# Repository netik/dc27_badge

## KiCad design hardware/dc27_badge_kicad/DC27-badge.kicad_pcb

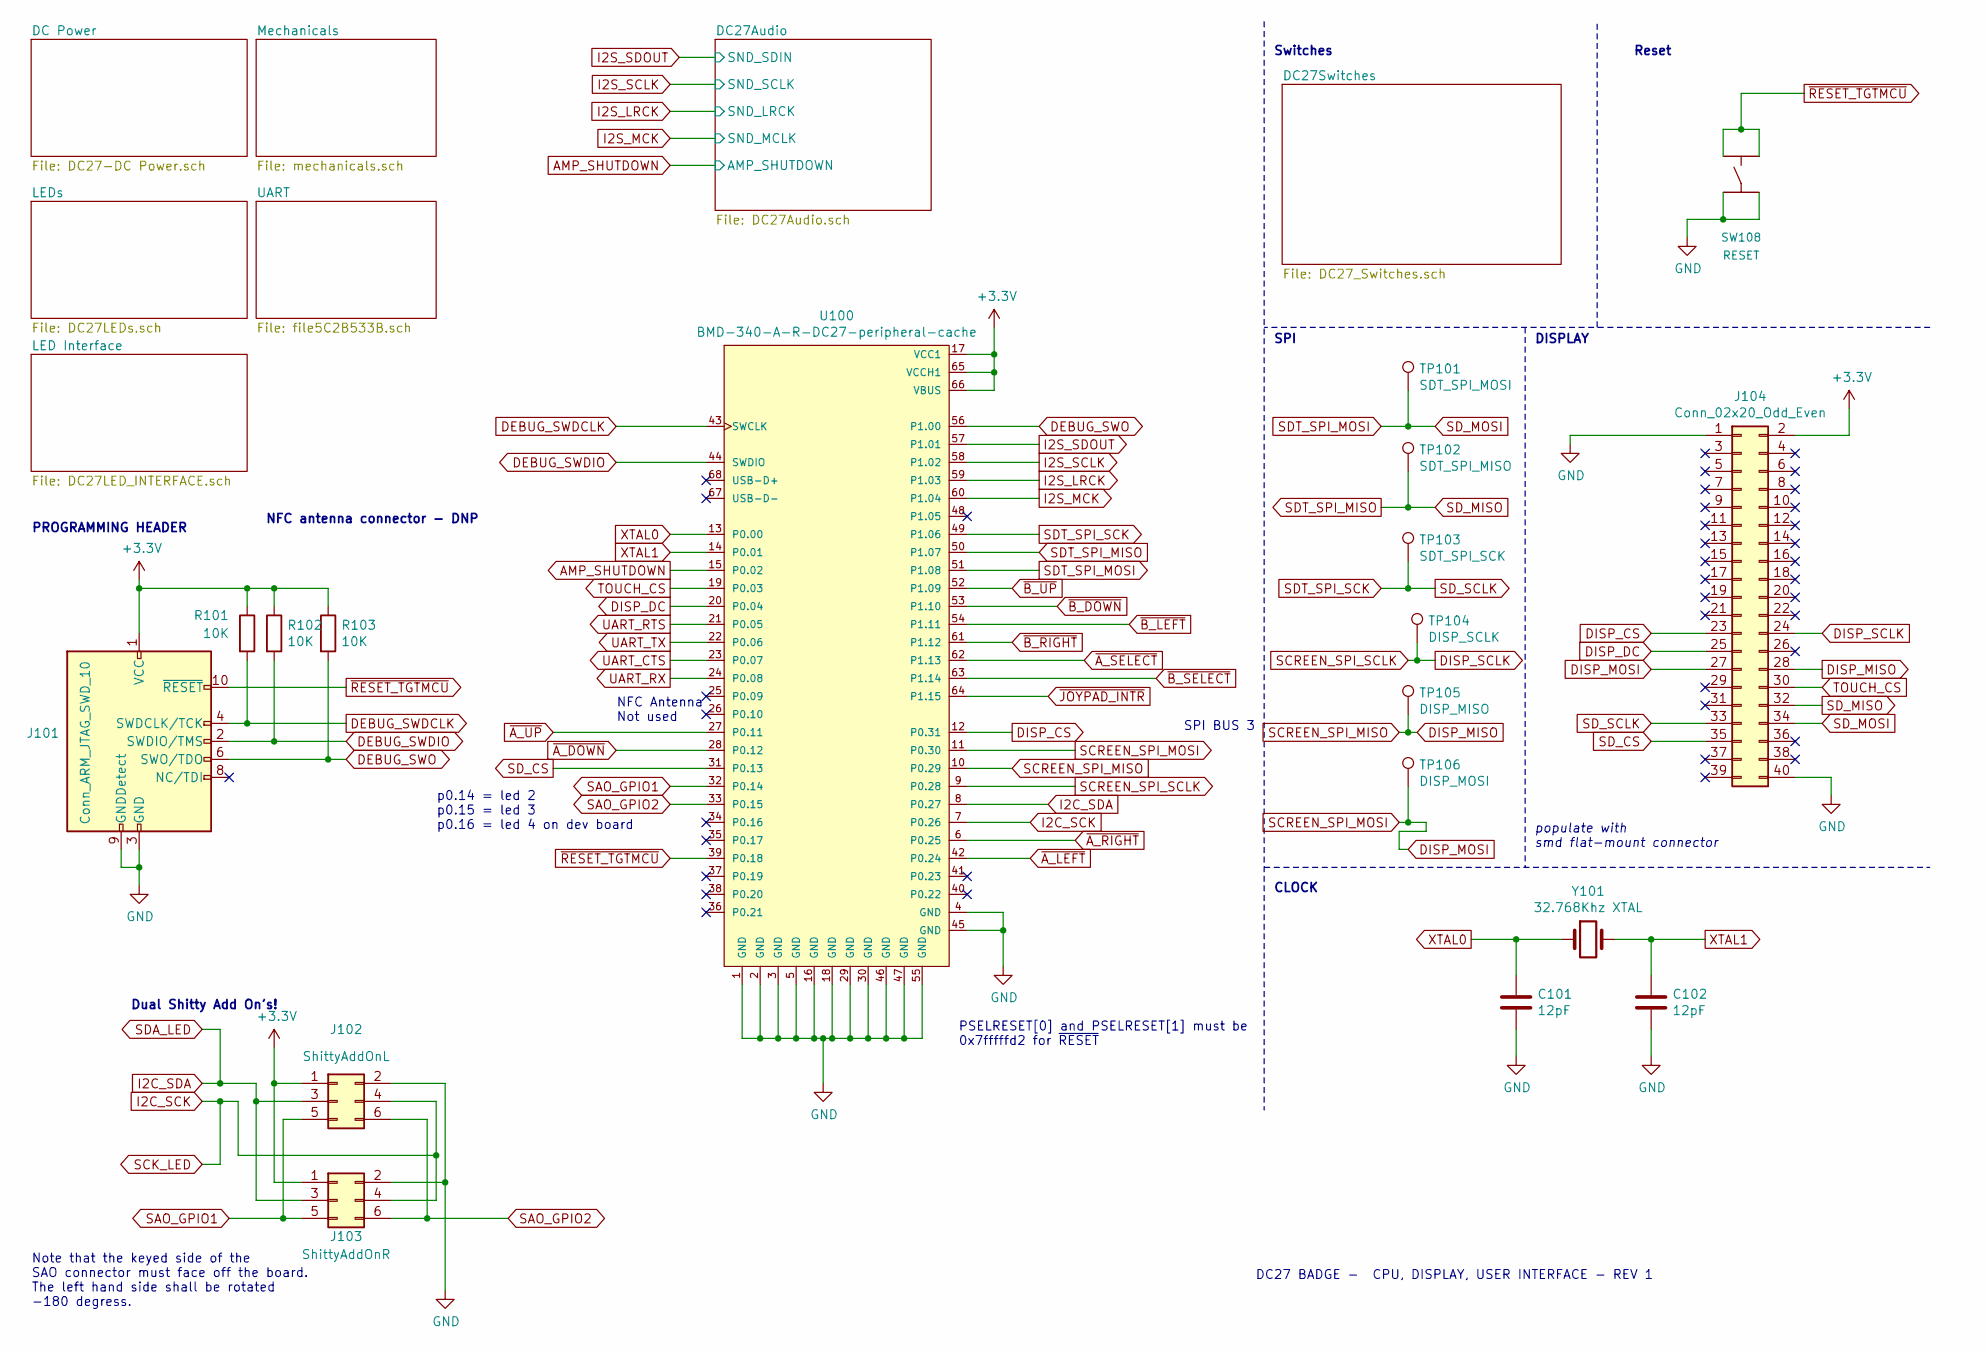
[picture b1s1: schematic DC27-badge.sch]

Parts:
C101, C102: 12pF; C_0805_2012Metric
J101: Conn_ARM_JTAG_SWD_10; PinHeader_2x05_P1.27mm_Vertical_SMD
J102: ShittyAddOnL; PinSocket_2x03_P2.54mm_Vertical
J103: ShittyAddOnR; PinSocket_2x03_P2.54mm_Vertical
J104: Conn_02x20_Odd_Even; SAMTEC-SSM-120-X-DV
R101, R102, R103: 10K; R_0603_1608Metric
SW108: RESET; MF_Switches-TACT4.2MM
TP101: SDT_SPI_MOSI; PinHeader_1x01_P2.54mm_Vertical
TP102: SDT_SPI_MISO; PinHeader_1x01_P2.54mm_Vertical
TP103: SDT_SPI_SCK; PinHeader_1x01_P2.54mm_Vertical
TP104: DISP_SCLK; PinHeader_1x01_P2.54mm_Vertical
TP105: DISP_MISO; PinHeader_1x01_P2.54mm_Vertical
TP106: DISP_MOSI; PinHeader_1x01_P2.54mm_Vertical
U100: BMD-340-A-R-DC27-peripheral-cache; RIGADO_BMD-340-A-R
Y101: 32.768Khz XTAL; Crystal_SMD_MicroCrystal_CC7V-T1A-2Pin_3.2x1.5mm

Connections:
AMP_SHUTDOWN: U100.15 (P0.02); also elsewhere on the board
AVCC: J101.1 (VCC), J102.1, J103.1, J104.2, R101.1, R102.1, R103.1, U100.17 (VCC1), U100.65 (VCCH1), U100.66 (VBUS); also elsewhere on the board
DEBUG_SWDCLK: J101.4 (SWDCLK/TCK), R101.2, U100.43 (SWCLK)
DEBUG_SWDIO: J101.2 (SWDIO/TMS), R102.2, U100.44 (SWDIO)
DEBUG_SWO: J101.6 (SWO/TDO), R103.2, U100.56 (P1.00)
DISP_CS: J104.23, U100.12 (P0.31)
DISP_DC: J104.25, U100.20 (P0.04)
DISP_MISO: J104.28, TP105.1, U100.10 (P0.29)
DISP_MOSI: J104.27, TP106.1, U100.11 (P0.30)
DISP_SCLK: J104.24, TP104.1, U100.9 (P0.28)
GND: C101.2, C102.2, J101.3 (GND), J101.5 (GND), J101.9 (GNDDetect), J102.2, J103.2, J104.1, J104.40, SW108.P$3, SW108.P$4, U100.1 (GND), U100.2 (GND), U100.3 (GND), U100.4 (GND), U100.5 (GND), U100.16 (GND), U100.18 (GND), U100.29 (GND), U100.30 (GND), U100.45 (GND), U100.46 (GND), U100.47 (GND), U100.55 (GND); also elsewhere on the board
I2C_SCK: J102.4, J103.4, U100.7 (P0.26); also elsewhere on the board
I2C_SDA: J102.3, J103.3, U100.8 (P0.27); also elsewhere on the board
I2S_LRCK: U100.59 (P1.03); also elsewhere on the board
I2S_MCK: U100.60 (P1.04); also elsewhere on the board
I2S_SCLK: U100.58 (P1.02); also elsewhere on the board
I2S_SDOUT: U100.57 (P1.01); also elsewhere on the board
SAO_GPIO1: J102.5, J103.5, U100.32 (P0.14)
SAO_GPIO2: J102.6, J103.6, U100.33 (P0.15)
SDT_SPI_MISO: J104.32, TP102.1, U100.50 (P1.07)
SDT_SPI_MOSI: J104.34, TP101.1, U100.51 (P1.08)
SDT_SPI_SCK: J104.33, TP103.1, U100.49 (P1.06)
SD_CS: J104.35, U100.31 (P0.13)
TOUCH_CS: J104.30, U100.19 (P0.03)
UART_CTS: U100.23 (P0.07); also elsewhere on the board
UART_RTS: U100.21 (P0.05); also elsewhere on the board
UART_RX: U100.24 (P0.08); also elsewhere on the board
UART_TX: U100.22 (P0.06); also elsewhere on the board
XTAL0: C101.1, U100.13 (P0.00), Y101.1
XTAL1: C102.1, U100.14 (P0.01), Y101.2
~A_DOWN: U100.28 (P0.12); also elsewhere on the board
~A_LEFT: U100.42 (P0.24); also elsewhere on the board
~A_RIGHT: U100.6 (P0.25); also elsewhere on the board
~A_SELECT: U100.62 (P1.13); also elsewhere on the board
~A_UP: U100.27 (P0.11); also elsewhere on the board
~B_DOWN: U100.53 (P1.10); also elsewhere on the board
~B_LEFT: U100.54 (P1.11); also elsewhere on the board
~B_RIGHT: U100.61 (P1.12); also elsewhere on the board
~B_SELECT: U100.63 (P1.14); also elsewhere on the board
~B_UP: U100.52 (P1.09); also elsewhere on the board
~JOYPAD_INTR: U100.64 (P1.15); also elsewhere on the board
~RESET_TGTMCU: J101.10 (~RESET~), SW108.P$1, SW108.P$2, U100.39 (P0.18)

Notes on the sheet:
DISPLAY
PROGRAMMING HEADER
populate with smd flat-mount connector
PSELRESET[0] and PSELRESET[1] must be 0x7fffffd2 for ~RESET
CLOCK
SPI
SPI BUS 3
NFC antenna connector - DNP
p0.14 = led 2 p0.15 = led 3 p0.16 = led 4 on dev board
DC27 BADGE - CPU, DISPLAY, USER INTERFACE - REV 1
NFC Antenna Not used
Dual Shitty Add On’s!
Switches
Reset
Note that the keyed side of the SAO connector must face off the board. The left hand side shall be rotated -180 degress.

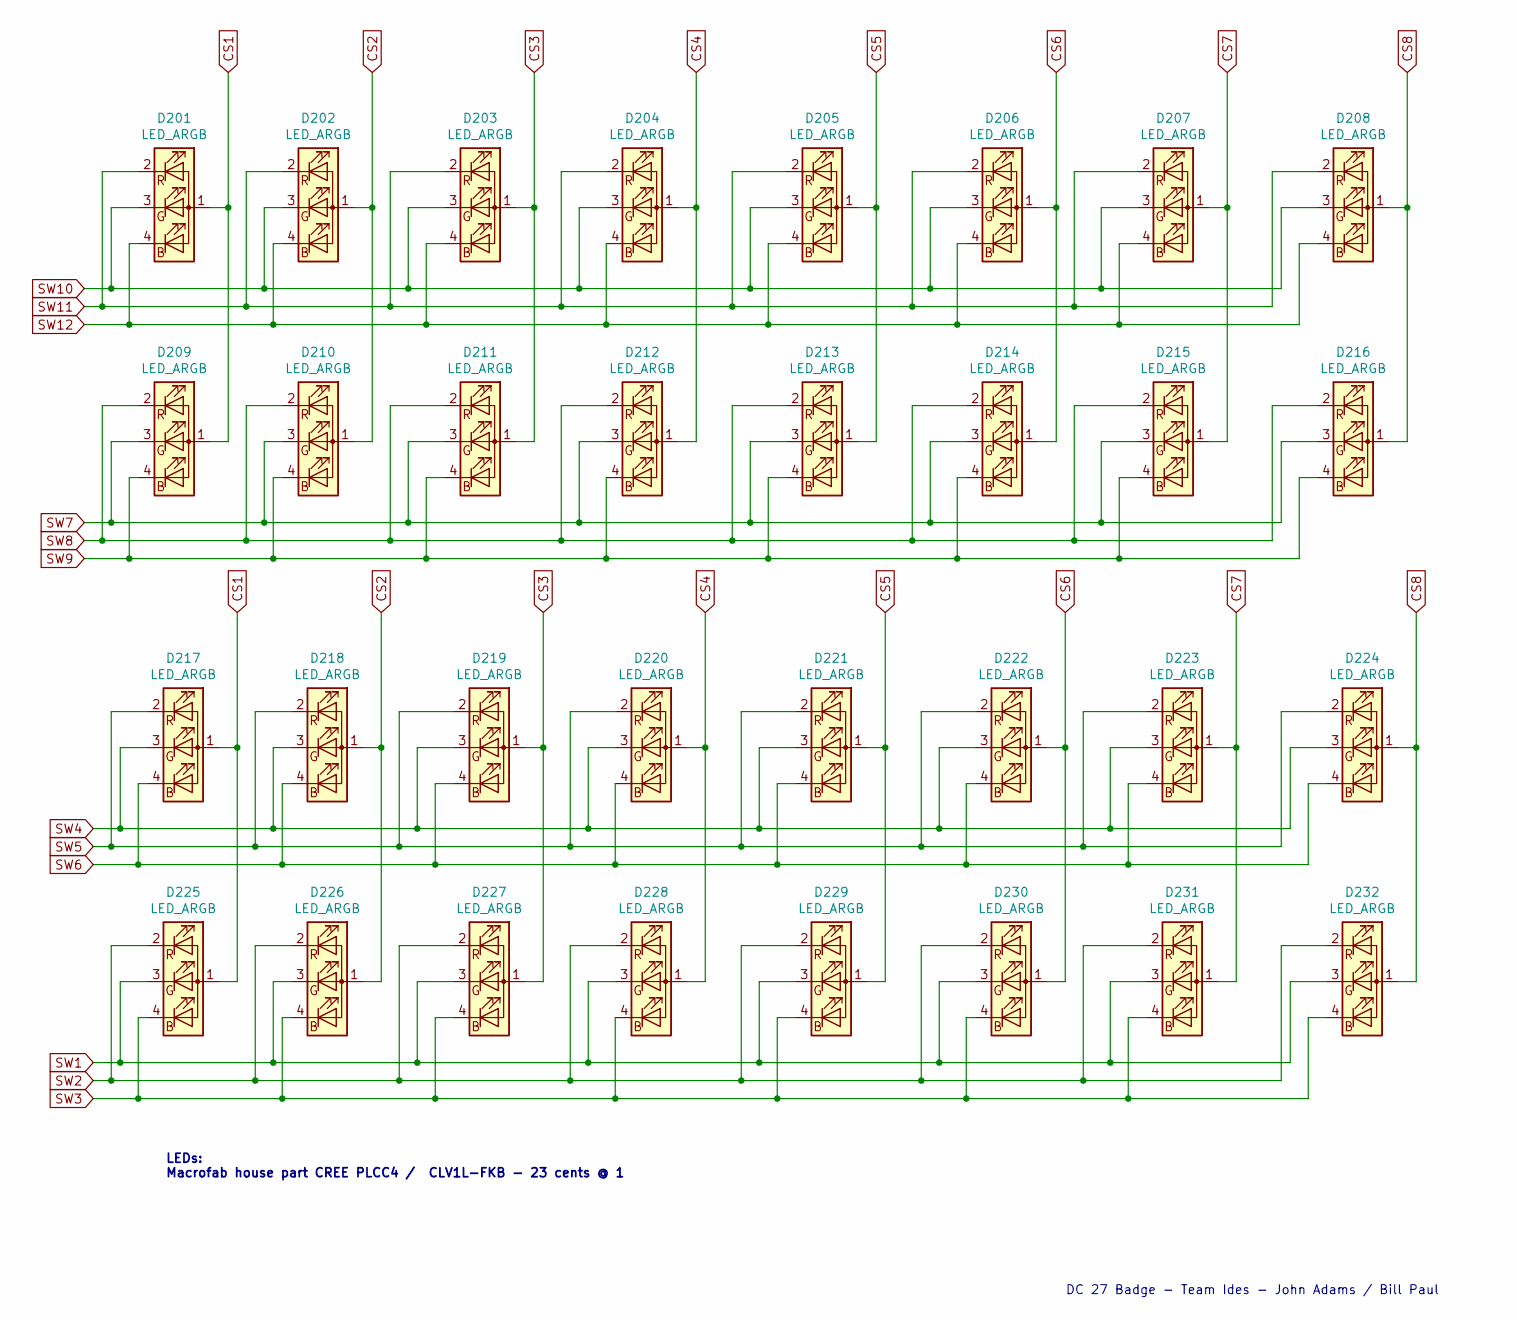
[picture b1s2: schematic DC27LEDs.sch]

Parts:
D201, D202, D203, D204, D205, D206, D207, D208, D209, D210, D211, D212, D213, D214, D215, D216, D217, D218, D219, D220, D221, D222, D223, D224, D225, D226, D227, D228, D229, D230, D231, D232: LED_ARGB; LED_Cree-PLCC4_3.2x2.8mm_CCW

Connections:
CS1: D201.1 (A), D209.1 (A), D217.1 (A), D225.1 (A); also elsewhere on the board
CS2: D202.1 (A), D210.1 (A), D218.1 (A), D226.1 (A); also elsewhere on the board
CS3: D203.1 (A), D211.1 (A), D219.1 (A), D227.1 (A); also elsewhere on the board
CS4: D204.1 (A), D212.1 (A), D220.1 (A), D228.1 (A); also elsewhere on the board
CS5: D205.1 (A), D213.1 (A), D221.1 (A), D229.1 (A); also elsewhere on the board
CS6: D206.1 (A), D214.1 (A), D222.1 (A), D230.1 (A); also elsewhere on the board
CS7: D207.1 (A), D215.1 (A), D223.1 (A), D231.1 (A); also elsewhere on the board
CS8: D208.1 (A), D216.1 (A), D224.1 (A), D232.1 (A); also elsewhere on the board
SW1: D225.3 (GK), D226.3 (GK), D227.3 (GK), D228.3 (GK), D229.3 (GK), D230.3 (GK), D231.3 (GK), D232.3 (GK); also elsewhere on the board
SW2: D225.2 (RK), D226.2 (RK), D227.2 (RK), D228.2 (RK), D229.2 (RK), D230.2 (RK), D231.2 (RK), D232.2 (RK); also elsewhere on the board
SW3: D225.4 (BK), D226.4 (BK), D227.4 (BK), D228.4 (BK), D229.4 (BK), D230.4 (BK), D231.4 (BK), D232.4 (BK); also elsewhere on the board
SW4: D217.3 (GK), D218.3 (GK), D219.3 (GK), D220.3 (GK), D221.3 (GK), D222.3 (GK), D223.3 (GK), D224.3 (GK); also elsewhere on the board
SW5: D217.2 (RK), D218.2 (RK), D219.2 (RK), D220.2 (RK), D221.2 (RK), D222.2 (RK), D223.2 (RK), D224.2 (RK); also elsewhere on the board
SW6: D217.4 (BK), D218.4 (BK), D219.4 (BK), D220.4 (BK), D221.4 (BK), D222.4 (BK), D223.4 (BK), D224.4 (BK); also elsewhere on the board
SW7: D209.3 (GK), D210.3 (GK), D211.3 (GK), D212.3 (GK), D213.3 (GK), D214.3 (GK), D215.3 (GK), D216.3 (GK); also elsewhere on the board
SW8: D209.2 (RK), D210.2 (RK), D211.2 (RK), D212.2 (RK), D213.2 (RK), D214.2 (RK), D215.2 (RK), D216.2 (RK); also elsewhere on the board
SW9: D209.4 (BK), D210.4 (BK), D211.4 (BK), D212.4 (BK), D213.4 (BK), D214.4 (BK), D215.4 (BK), D216.4 (BK); also elsewhere on the board
SW10: D201.3 (GK), D202.3 (GK), D203.3 (GK), D204.3 (GK), D205.3 (GK), D206.3 (GK), D207.3 (GK), D208.3 (GK); also elsewhere on the board
SW11: D201.2 (RK), D202.2 (RK), D203.2 (RK), D204.2 (RK), D205.2 (RK), D206.2 (RK), D207.2 (RK), D208.2 (RK); also elsewhere on the board
SW12: D201.4 (BK), D202.4 (BK), D203.4 (BK), D204.4 (BK), D205.4 (BK), D206.4 (BK), D207.4 (BK), D208.4 (BK); also elsewhere on the board

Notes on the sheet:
LEDs: Macrofab house part CREE PLCC4 / CLV1L-FKB - 23 cents @ 1
DC 27 Badge - Team Ides - John Adams / Bill Paul

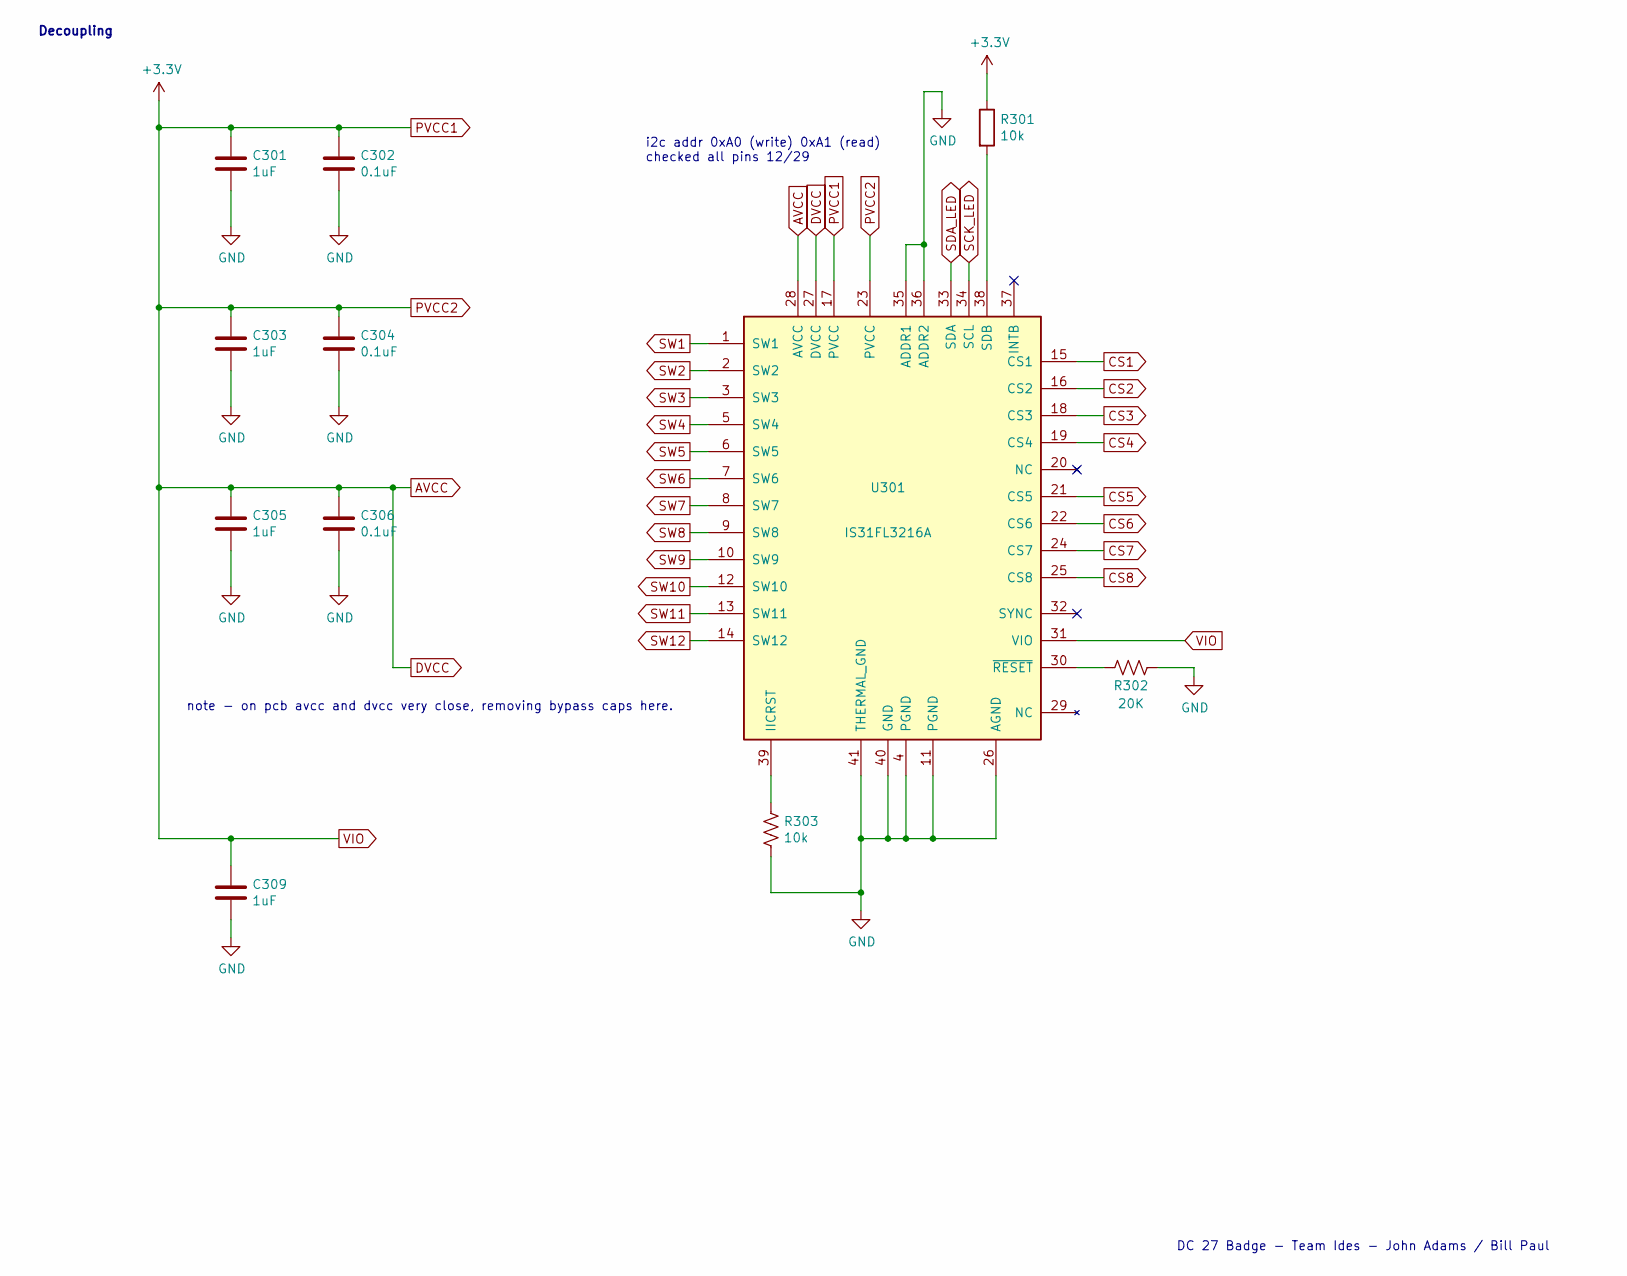
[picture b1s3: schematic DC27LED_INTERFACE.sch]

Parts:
C301, C303, C305, C309: 1uF; C_0603_1608Metric
C302, C304, C306: 0.1uF; C_0603_1608Metric
R301, R303: 10k; R_0603_1608Metric
R302: 20K; R_0603_1608Metric
U301: IS31FL3216A; QFN-40-1EP_5x5mm_P0.4mm_EP3.6x3.6mm

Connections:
AVCC: C301.1, C302.1, C303.1, C304.1, C305.1, C306.1, C309.1, R301.1, U301.17 (PVCC), U301.23 (PVCC), U301.27 (DVCC), U301.28 (AVCC), U301.31 (VIO); also elsewhere on the board
CS1: U301.15 (CS1); also elsewhere on the board
CS2: U301.16 (CS2); also elsewhere on the board
CS3: U301.18 (CS3); also elsewhere on the board
CS4: U301.19 (CS4); also elsewhere on the board
CS5: U301.21 (CS5); also elsewhere on the board
CS6: U301.22 (CS6); also elsewhere on the board
CS7: U301.24 (CS7); also elsewhere on the board
CS8: U301.25 (CS8); also elsewhere on the board
GND: C301.2, C302.2, C303.2, C304.2, C305.2, C306.2, C309.2, R302.1, R303.2, U301.4 (PGND), U301.11 (PGND), U301.26 (AGND), U301.35 (ADDR1), U301.36 (ADDR2), U301.40 (GND), U301.41 (THERMAL_GND); also elsewhere on the board
I2C_SCK: U301.34 (SCL); also elsewhere on the board
I2C_SDA: U301.33 (SDA); also elsewhere on the board
unnamed: R301.2, U301.38 (SDB)
unnamed: R302.2, U301.30 (~RESET)
unnamed: R303.1, U301.39 (IICRST)
SW1: U301.1 (SW1); also elsewhere on the board
SW2: U301.2 (SW2); also elsewhere on the board
SW3: U301.3 (SW3); also elsewhere on the board
SW4: U301.5 (SW4); also elsewhere on the board
SW5: U301.6 (SW5); also elsewhere on the board
SW6: U301.7 (SW6); also elsewhere on the board
SW7: U301.8 (SW7); also elsewhere on the board
SW8: U301.9 (SW8); also elsewhere on the board
SW9: U301.10 (SW9); also elsewhere on the board
SW10: U301.12 (SW10); also elsewhere on the board
SW11: U301.13 (SW11); also elsewhere on the board
SW12: U301.14 (SW12); also elsewhere on the board

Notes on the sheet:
Decoupling
DC 27 Badge - Team Ides - John Adams / Bill Paul
i2c addr 0xA0 (write) 0xA1 (read) checked all pins 12/29
note - on pcb avcc and dvcc very close, removing bypass caps here.

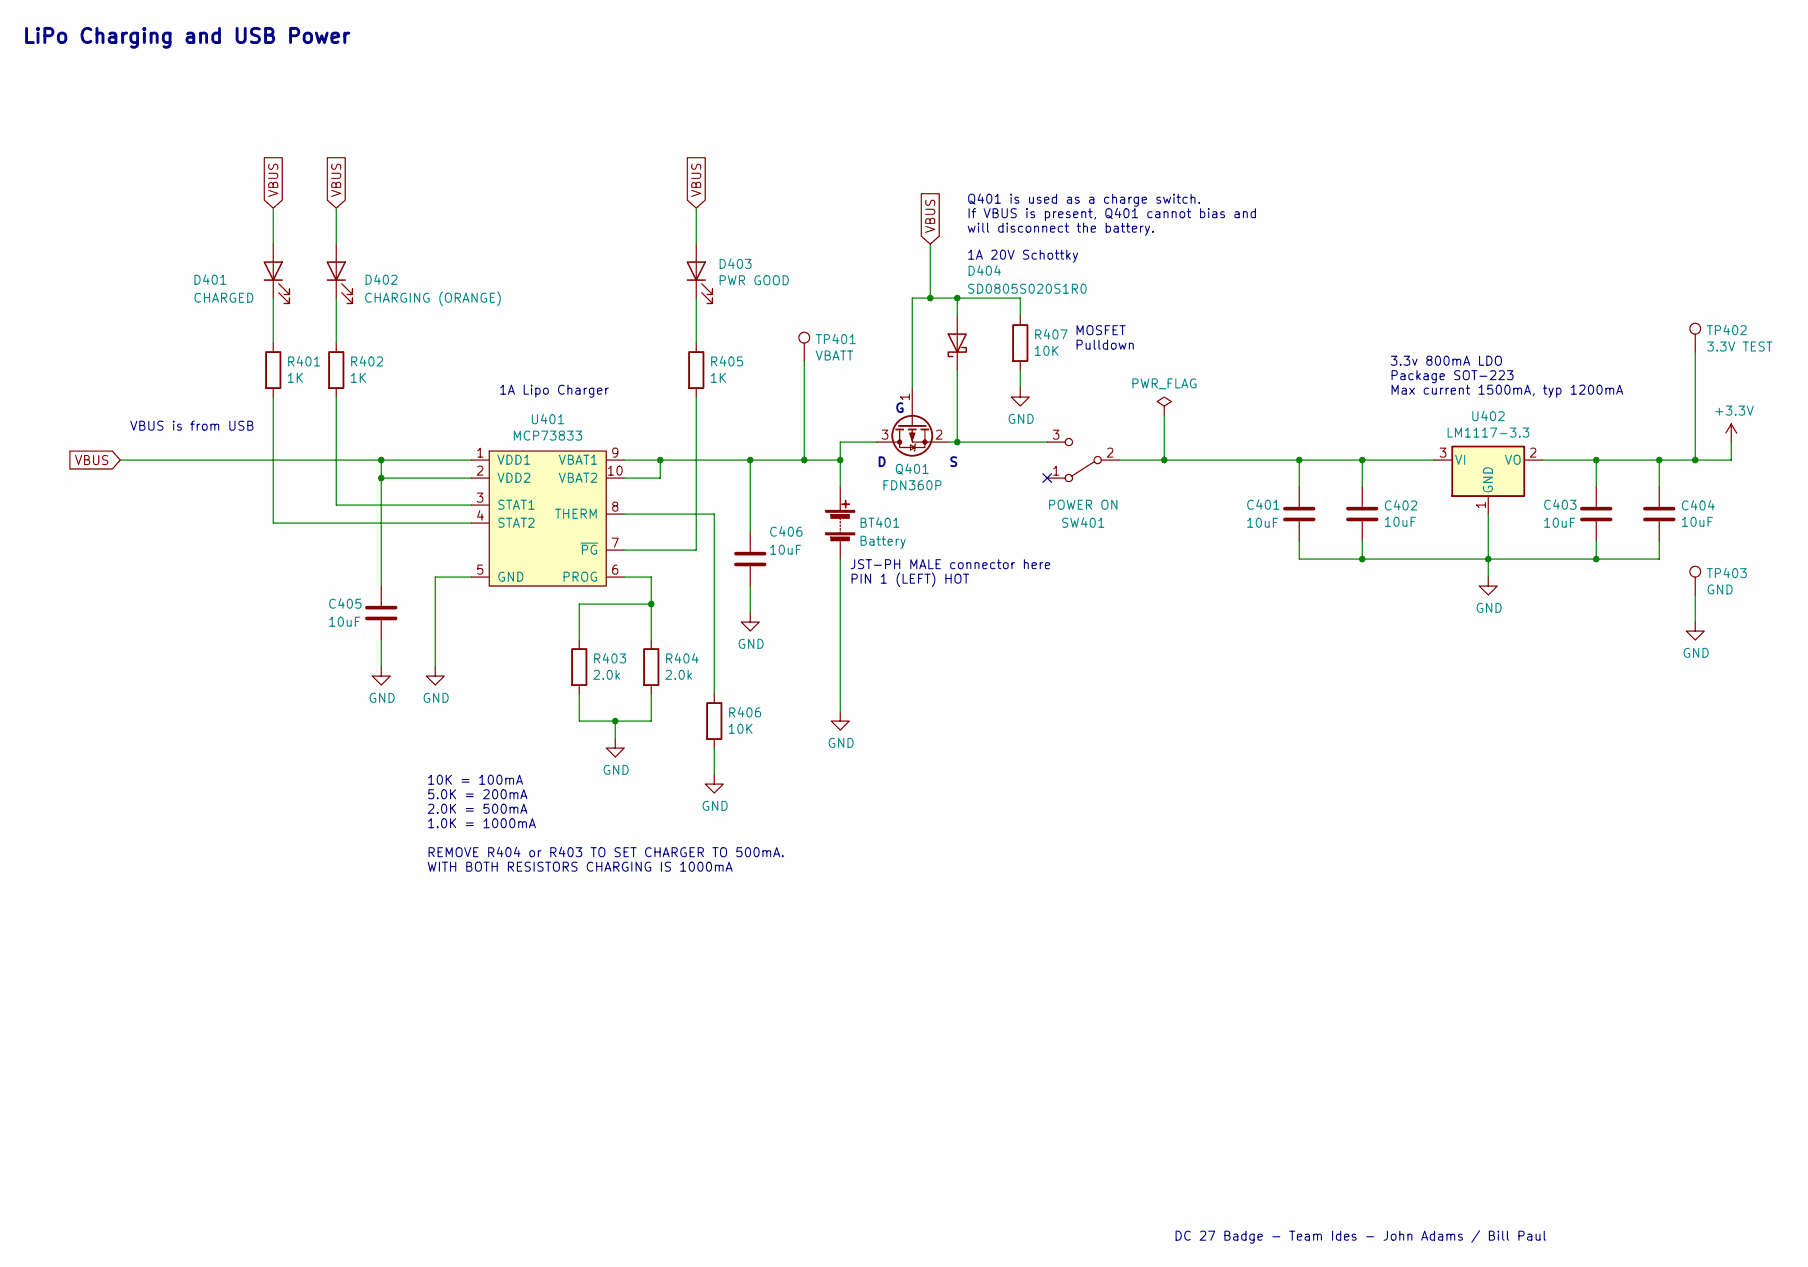
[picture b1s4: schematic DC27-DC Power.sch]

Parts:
BT401: Battery; JST_PH_S2B-PH-SM4-TB_1x02-1MP_P2.00mm_Horizontal
C401, C402, C403, C404, C405, C406: 10uF; C_1206_3216Metric
D401: CHARGED; D_0603_1608Metric
D402: CHARGING (ORANGE); D_0603_1608Metric
D403: PWR GOOD; D_0603_1608Metric
D404: SD0805S020S1R0; D_0805_2012Metric
Q401: FDN360P; SOT-23
R401, R402, R405: 1K; R_0603_1608Metric
R403, R404: 2.0k; R_0603_1608Metric
R406, R407: 10K; R_0603_1608Metric
SW401: POWER ON; SW_SPDT_PCM12
TP401: VBATT; PinHeader_1x01_P2.54mm_Vertical
TP402: 3.3V TEST; PinHeader_1x01_P2.54mm_Vertical
TP403: GND; PinHeader_1x01_P2.54mm_Vertical
U401: MCP73833; MSOP-10_3x3mm_P0.5mm
U402: LM1117-3.3; SOT-223

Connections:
AVCC: C403.1, C404.1, TP402.1, U402.2 (VO); also elsewhere on the board
GND: BT401.2 (-), C401.2, C402.2, C403.2, C404.2, C405.2, C406.2, R403.2, R404.2, R406.2, R407.2, TP403.1, U401.5 (GND), U402.1 (GND); also elsewhere on the board
unnamed: BT401.1 (+), C406.1, Q401.3 (D), TP401.1, U401.9 (VBAT1), U401.10 (VBAT2)
unnamed: C401.1, C402.1, SW401.2 (B), U402.3 (VI)
unnamed: D401.1 (K), R401.1
unnamed: D402.1 (K), R402.1
unnamed: D403.1 (K), R405.1
unnamed: D404.1 (K), Q401.2 (S), SW401.3 (C)
unnamed: R401.2, U401.4 (STAT2)
unnamed: R402.2, U401.3 (STAT1)
unnamed: R403.1, R404.1, U401.6 (PROG)
unnamed: R405.2, U401.7 (~PG)
unnamed: R406.1, U401.8 (THERM)
VBUS: C405.1, D401.2 (A), D402.2 (A), D403.2 (A), D404.2 (A), Q401.1 (G), R407.1, U401.1 (VDD1), U401.2 (VDD2); also elsewhere on the board

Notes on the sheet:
LiPo Charging and USB Power
DC 27 Badge - Team Ides - John Adams / Bill Paul
3.3v 800mA LDO Package SOT-223 Max current 1500mA, typ 1200mA
VBUS is from USB
JST-PH MALE connector here PIN 1 (LEFT) HOT
1A Lipo Charger
10K = 100mA 5.0K = 200mA 2.0K = 500mA 1.0K = 1000mA REMOVE R404 or R403 TO SET CHARGER TO 500mA. WITH BOTH RESISTORS CHARGING IS 1000mA
1A 20V Schottky
MOSFET Pulldown
Q401 is used as a charge switch. If VBUS is present, Q401 cannot bias and will disconnect the battery.

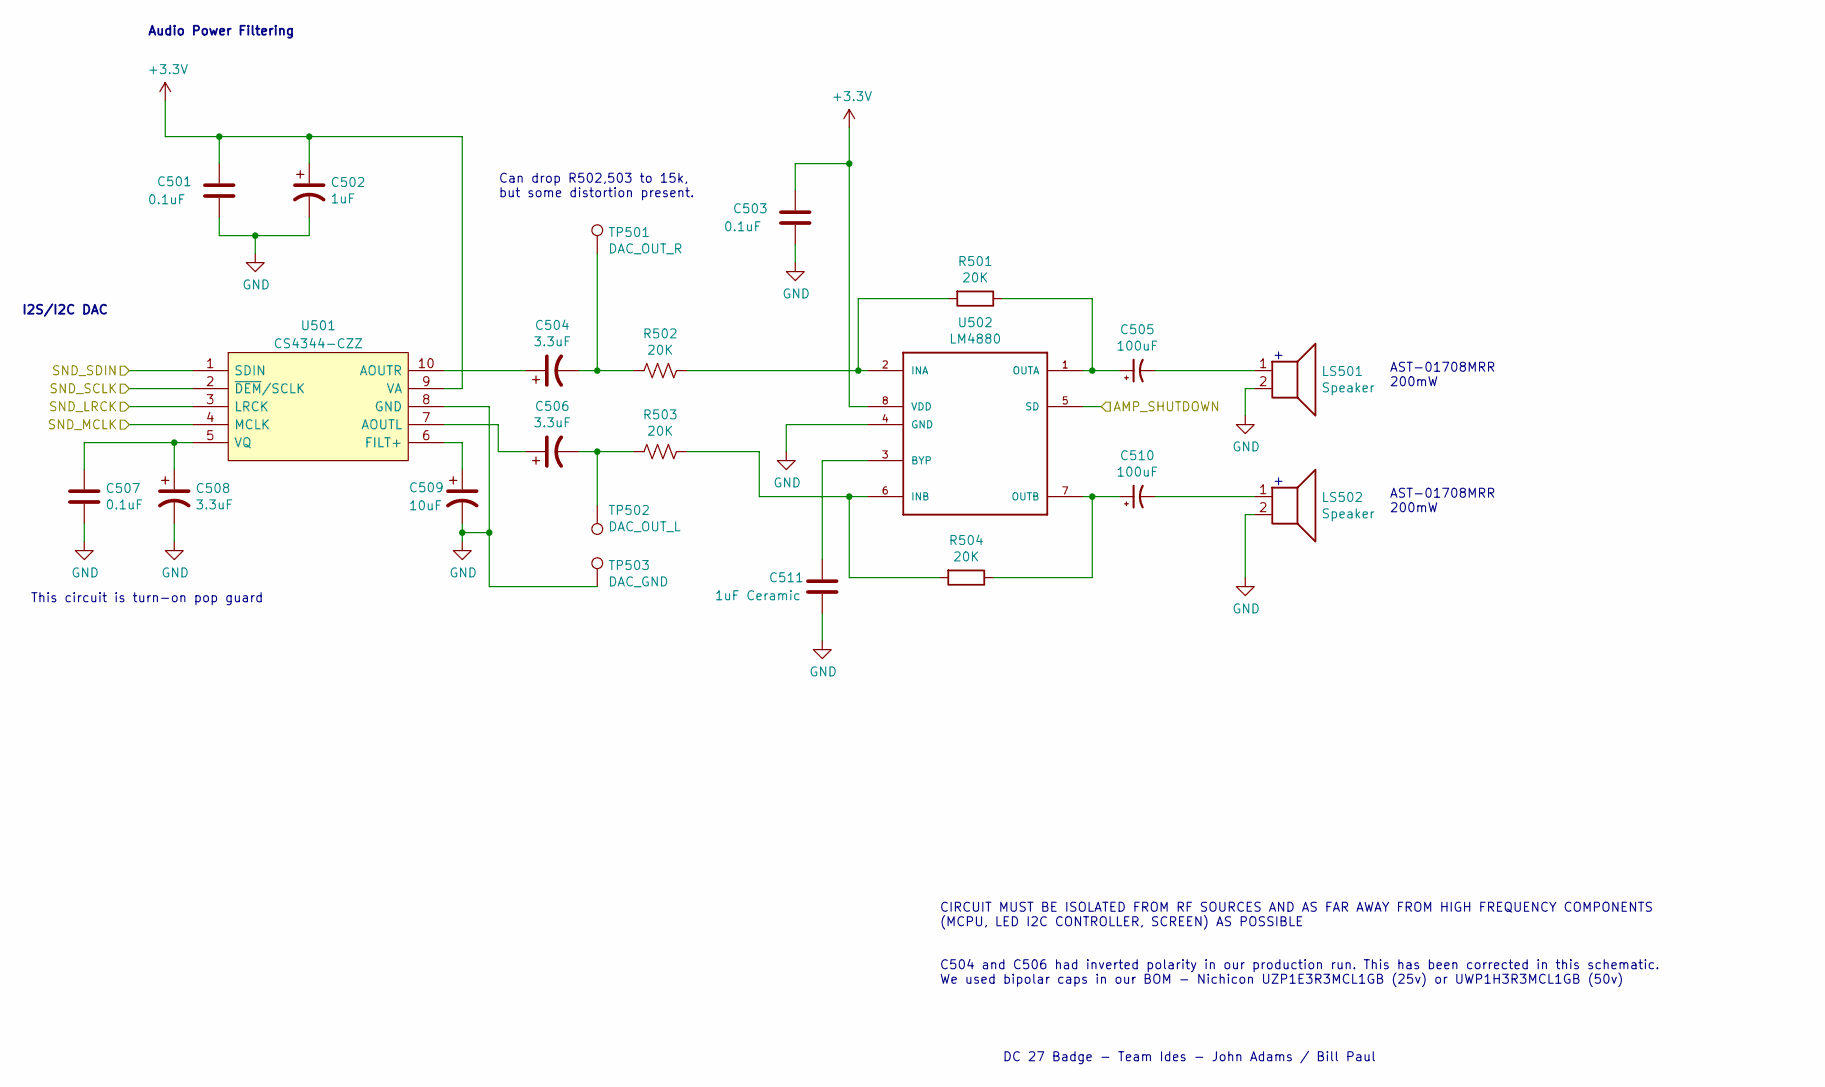
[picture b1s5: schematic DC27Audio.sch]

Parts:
C501, C503, C507: 0.1uF; C_0603_1608Metric
C502: 1uF; C_0603_1608Metric
C504, C506, C508: 3.3uF; CP_Elec_5x5.3
C505, C510: 100uF; MF_Passives-CP6.3MM
C509: 10uF; MF_Passives-CP4MM
C511: 1uF Ceramic; C_0603_1608Metric
LS501, LS502: Speaker; AST-01708-MRR
R501, R502, R503, R504: 20K; R_0805_2012Metric
TP501: DAC_OUT_R; TestPoint_Pad_D2.0mm
TP502: DAC_OUT_L; TestPoint_Pad_D2.0mm
TP503: DAC_GND; TestPoint_Pad_D2.0mm
U501: CS4344-CZZ; TSSOP-10_3x3mm_Pitch0.5mm; Manufacturer_Part_Number CS4344-CZZ
U502: LM4880; SOIC-8_3.9x4.9mm_P1.27mm

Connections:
AMP_SHUTDOWN: U502.5 (SD); also elsewhere on the board
AVCC: C501.1, C502.1, C503.1, U501.9 (VA), U502.8 (VDD); also elsewhere on the board
GND: C501.2, C502.2, C503.2, C507.2, C508.2, C509.2, C511.2, LS501.2, LS502.2, TP503.1, U501.8 (GND), U502.4 (GND); also elsewhere on the board
I2S_LRCK: U501.3 (LRCK); also elsewhere on the board
I2S_MCK: U501.4 (MCLK); also elsewhere on the board
I2S_SCLK: U501.2 (~DEM~/SCLK); also elsewhere on the board
I2S_SDOUT: U501.1 (SDIN); also elsewhere on the board
unnamed: C504.1, U501.10 (AOUTR)
unnamed: C504.2, R502.2, TP501.1
unnamed: C505.1, R501.1, U502.1 (OUTA)
unnamed: C505.2, LS501.1
unnamed: C506.1, U501.7 (AOUTL)
unnamed: C506.2, R503.2, TP502.1
unnamed: C507.1, C508.1, U501.5 (VQ)
unnamed: C509.1, U501.6 (FILT+)
unnamed: C510.1, R504.1, U502.7 (OUTB)
unnamed: C510.2, LS502.1
unnamed: C511.1, U502.3 (BYP)
unnamed: R501.2, R502.1, U502.2 (INA)
unnamed: R503.1, R504.2, U502.6 (INB)

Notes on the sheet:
DC 27 Badge - Team Ides - John Adams / Bill Paul
I2S/I2C DAC
Audio Power Filtering
CIRCUIT MUST BE ISOLATED FROM RF SOURCES AND AS FAR AWAY FROM HIGH FREQUENCY COMPONENTS (MCPU, LED I2C CONTROLLER, SCREEN) AS POSSIBLE
AST-01708MRR 200mW
This circuit is turn-on pop guard
Can drop R502,503 to 15k, but some distortion present.
C504 and C506 had inverted polarity in our production run. This has been corrected in this schematic. We used bipolar caps in our BOM - Nichicon UZP1E3R3MCL1GB (25v) or UWP1H3R3MCL1GB (50v)

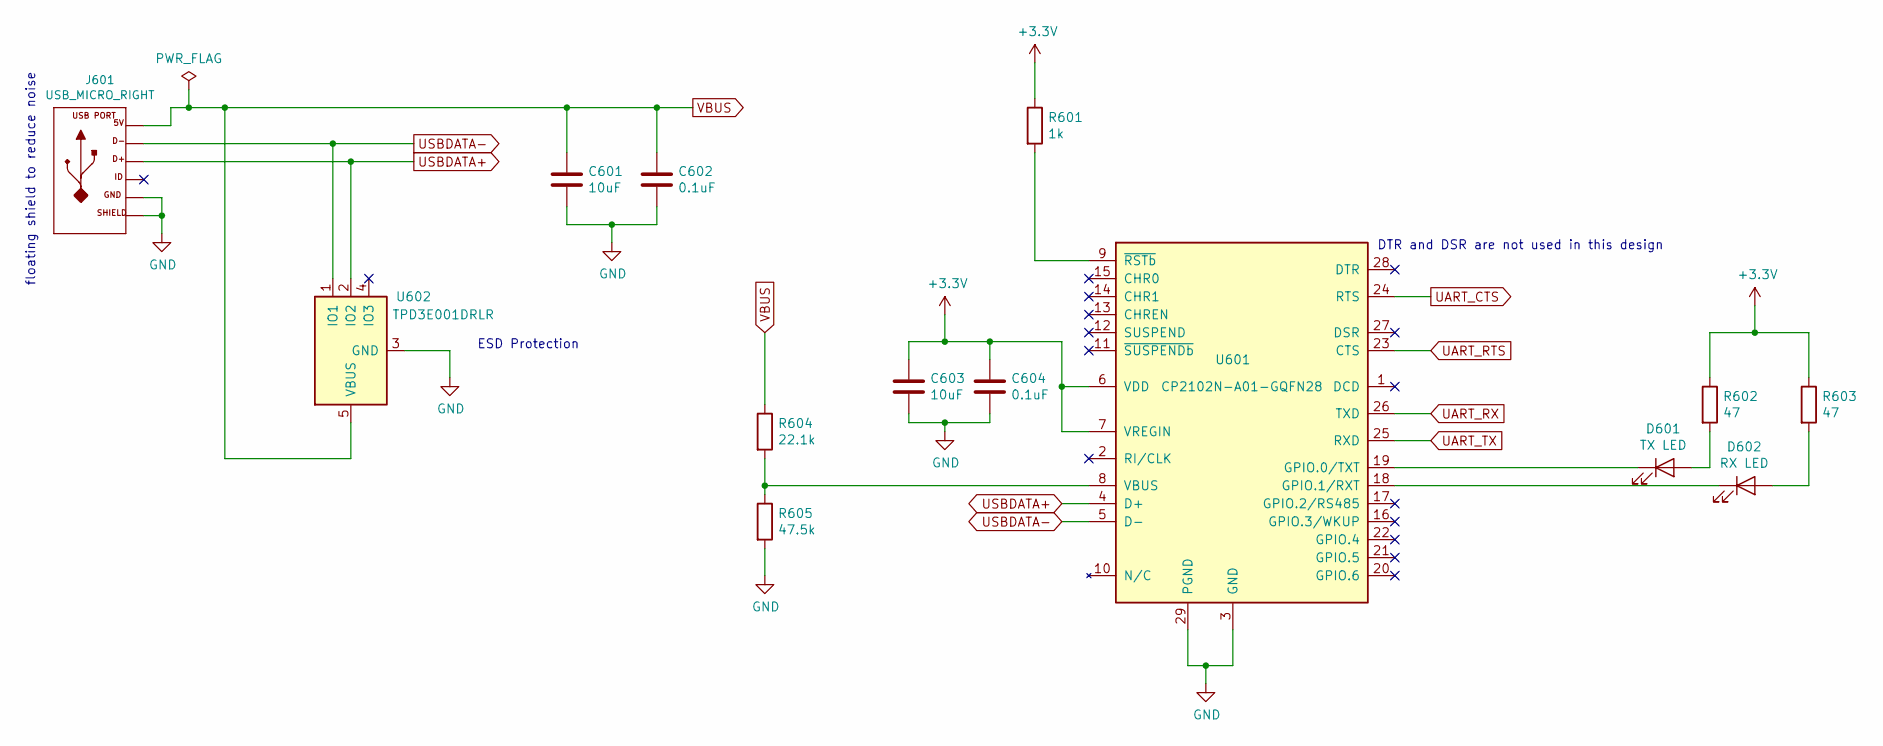
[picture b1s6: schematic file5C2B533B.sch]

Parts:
C601, C603: 10uF; C_1206_3216Metric
C602, C604: 0.1uF; C_0603_1608Metric
D601: TX LED; D_0603_1608Metric
D602: RX LED; D_0603_1608Metric
J601: USB_MICRO_RIGHT; MF_Connectors-MICROUSB-RIGHT
R601: 1k; R_0603_1608Metric
R602, R603: 47; R_0603_1608Metric
R604: 22.1k; R_0603_1608Metric
R605: 47.5k; R_0603_1608Metric
U601: CP2102N-A01-GQFN28; QFN-28-1EP_5x5mm_P0.5mm_EP3.35x3.35mm_ThermalVias
U602: TPD3E001DRLR; SOT-553

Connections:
AVCC: C603.1, C604.1, R601.1, R602.1, R603.1, U601.6 (VDD), U601.7 (VREGIN); also elsewhere on the board
GND: C601.2, C602.2, C603.2, C604.2, J601.5 (GND), J601.S1 (SLD), J601.S2 (SLD), J601.S3 (SLD), J601.S4 (SLD), J601.S5 (SLD), J601.S6 (SLD), R605.2, U601.3 (GND), U601.29 (PGND), U602.3 (GND); also elsewhere on the board
unnamed: D601.1 (K), U601.19 (GPIO.0/TXT)
unnamed: D601.2 (A), R602.2
unnamed: D602.1 (K), U601.18 (GPIO.1/RXT)
unnamed: D602.2 (A), R603.2
unnamed: R601.2, U601.9 (~RSTb)
unnamed: R604.2, R605.1, U601.8 (VBUS)
UART_CTS: U601.24 (RTS); also elsewhere on the board
UART_RTS: U601.23 (CTS); also elsewhere on the board
UART_RX: U601.26 (TXD); also elsewhere on the board
UART_TX: U601.25 (RXD); also elsewhere on the board
USBDATA+: J601.3 (D+), U601.4 (D+), U602.2 (IO2)
USBDATA-: J601.2 (D-), U601.5 (D-), U602.1 (IO1)
VBUS: C601.1, C602.1, J601.1 (5V), R604.1, U602.5 (VBUS); also elsewhere on the board

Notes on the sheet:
DTR and DSR are not used in this design
floating shield to reduce noise
ESD Protection

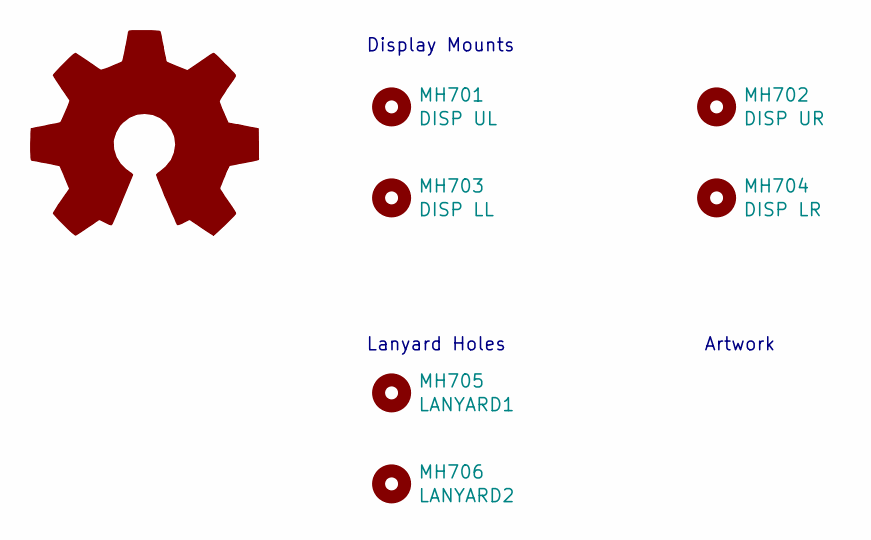
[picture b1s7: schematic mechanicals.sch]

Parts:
MH701: DISP UL; MountingHole_3.2mm_M3_DIN965
MH702: DISP UR; MountingHole_3.2mm_M3_DIN965
MH703: DISP LL; MountingHole_3.2mm_M3_DIN965
MH704: DISP LR; MountingHole_3.2mm_M3_DIN965
MH705: LANYARD1; MountingHole_3.2mm_M3_DIN965
MH706: LANYARD2; MountingHole_3.2mm_M3_DIN965

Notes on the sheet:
Display Mounts
Lanyard Holes
Artwork

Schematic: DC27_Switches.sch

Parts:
D801, D802, D803, D804, D805: BAT54AW; SOT-323_SC-70
SW801, SW802: SKRHAAE010

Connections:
GND: SW801.5 (COM), SW802.5 (COM); also elsewhere on the board
~A_DOWN: D805.1, SW801.6 (D_DOWN); also elsewhere on the board
~A_LEFT: D802.1, SW801.3 (C_LEFT); also elsewhere on the board
~A_RIGHT: D804.1, SW801.4 (B_RIGHT); also elsewhere on the board
~A_SELECT: D803.1, SW801.2 (CENTER); also elsewhere on the board
~A_UP: D801.1, SW801.1 (A_UP); also elsewhere on the board
~B_DOWN: SW802.6 (D_DOWN); also elsewhere on the board
~B_LEFT: SW802.3 (C_LEFT); also elsewhere on the board
~B_RIGHT: SW802.4 (B_RIGHT); also elsewhere on the board
~B_SELECT: SW802.2 (CENTER); also elsewhere on the board
~B_UP: SW802.1 (A_UP); also elsewhere on the board
~JOYPAD_INTR: D801.2, D802.2, D803.2, D804.2, D805.2; also elsewhere on the board
